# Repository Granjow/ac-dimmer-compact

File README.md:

# AC Dimmer

This is the Kicad PCB plus code for a halogen bulb dimmer
which we created for [Geheimgang 188](https://www.geheimgang.ch/).

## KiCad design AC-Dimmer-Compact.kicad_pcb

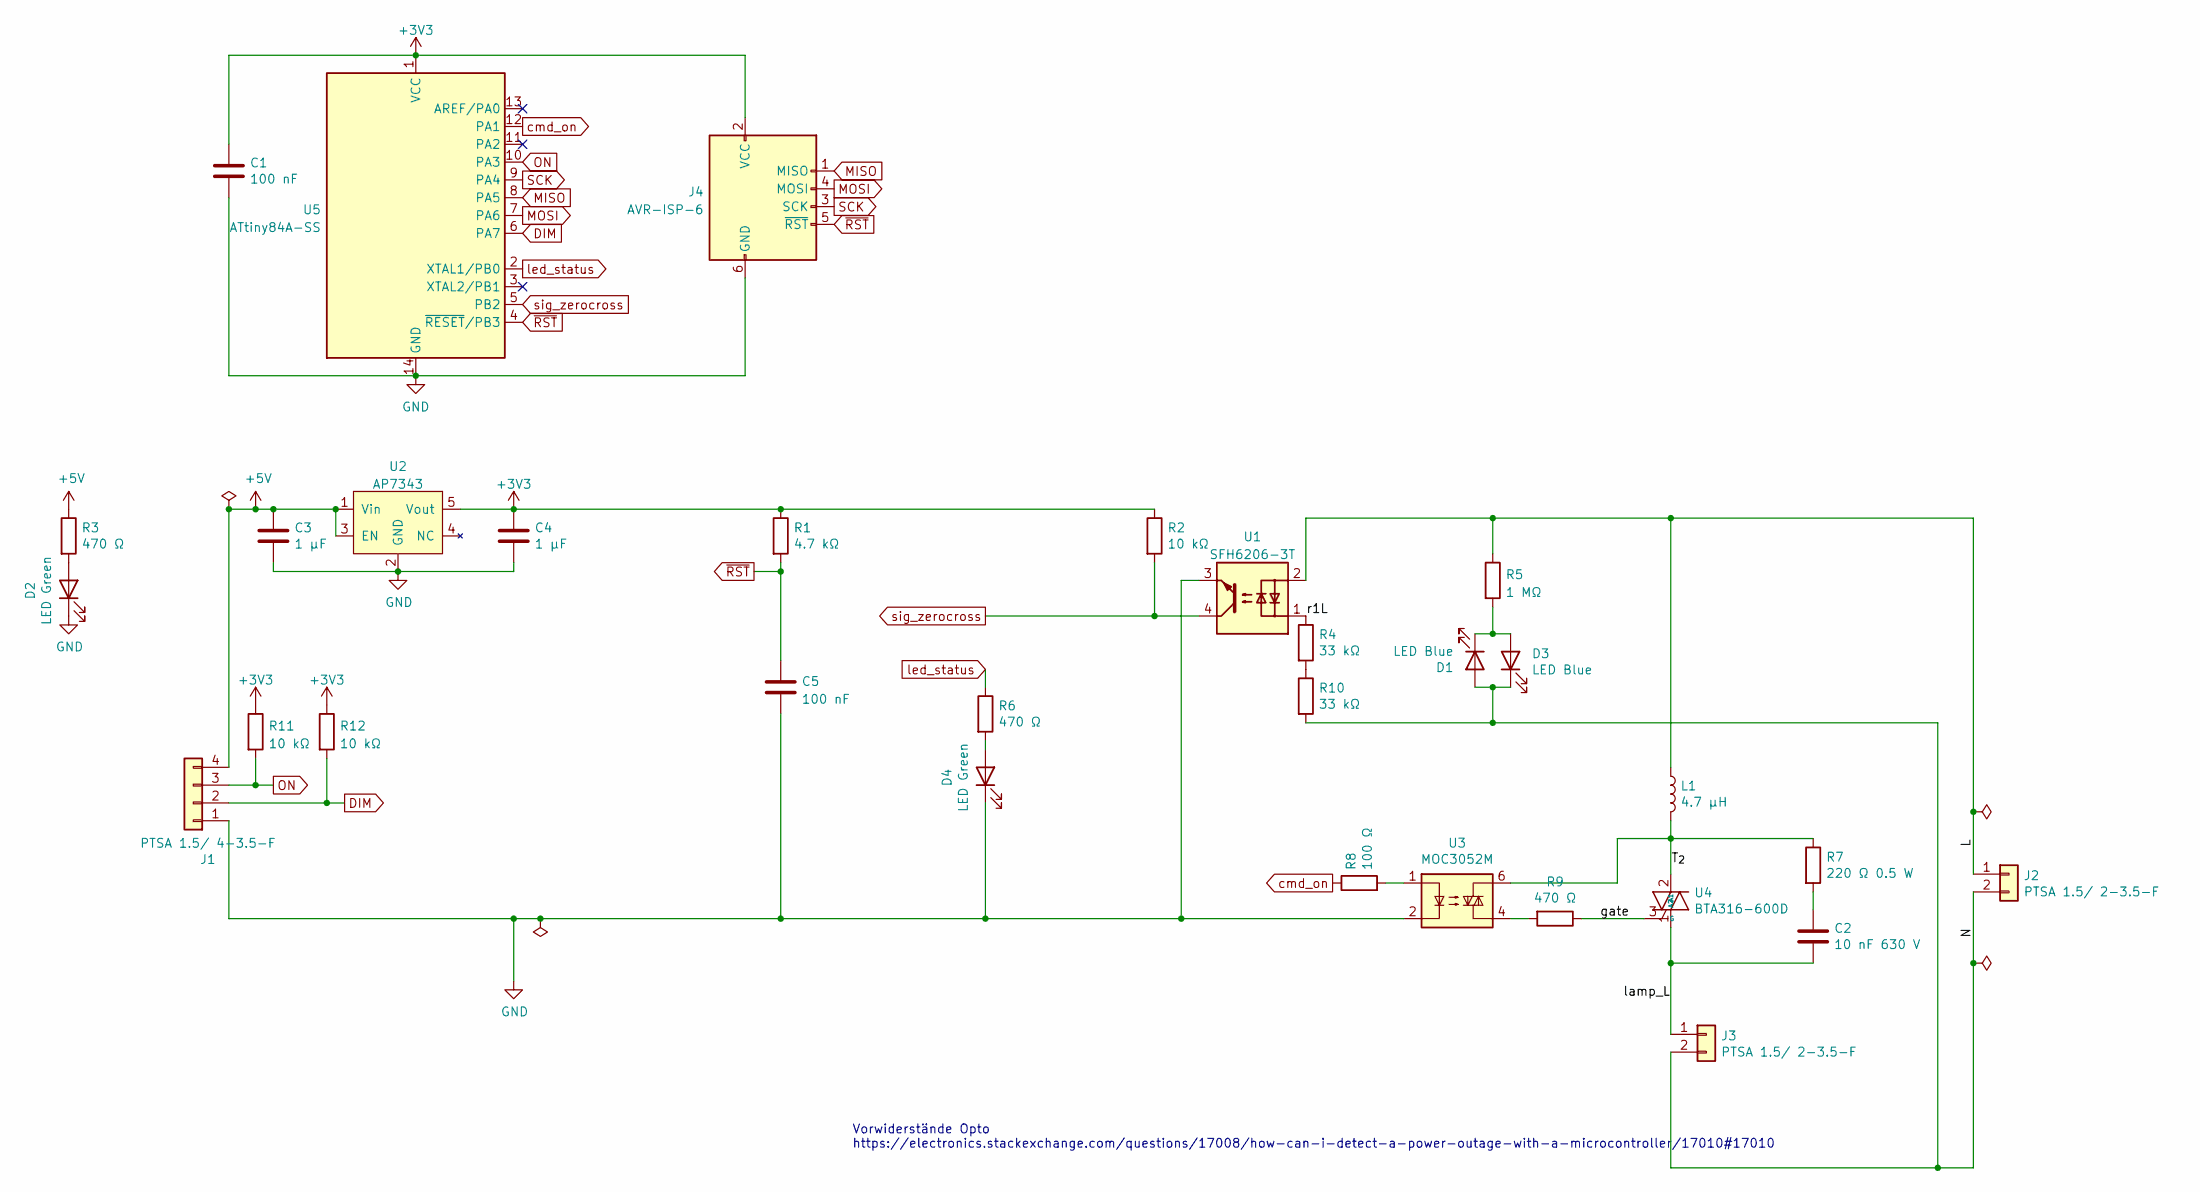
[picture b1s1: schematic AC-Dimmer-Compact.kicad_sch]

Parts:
C1, C5: 100 nF; C_0805_2012Metric_Pad1.18x1.45mm_HandSolder
C2: 10 nF 630 V; C_Rect_L7.2mm_W8.5mm_P5.00mm_FKP2_FKP2_MKS2_MKP2
C3, C4: 1 µF; C_0805_2012Metric_Pad1.15x1.40mm_HandSolder
D1, D3: LED Blue; LED_0805_2012Metric_Pad1.15x1.40mm_HandSolder
D2, D4: LED Green; LED_0805_2012Metric_Pad1.15x1.40mm_HandSolder
J1: PTSA 1.5/ 4-3.5-F; Phoenix_PTSA-1,5_1x4_P3.5mm
J2, J3: PTSA 1.5/ 2-3.5-F; Phoenix_PTSA-1,5_1x2_P3.5mm
J4: AVR-ISP-6; PinHeader_2x03_P2.54mm_Vertical
L1: 4.7 µH; 4RCC-4R7M-F18.4mm
R1: 4.7 kΩ; R_0805_2012Metric_Pad1.15x1.40mm_HandSolder
R2, R11, R12: 10 kΩ; R_0805_2012Metric_Pad1.20x1.40mm_HandSolder
R3, R6, R9: 470 Ω; R_0805_2012Metric_Pad1.15x1.40mm_HandSolder
R4, R10: 33 kΩ; R_2010_5025Metric_Pad1.40x2.65mm_HandSolder
R5: 1 MΩ; R_0805_2012Metric_Pad1.20x1.40mm_HandSolder
R7: 220 Ω 0.5 W; R_0805_2012Metric_Pad1.15x1.40mm_HandSolder
R8: 100 Ω; R_0805_2012Metric_Pad1.15x1.40mm_HandSolder
U1: SFH6206-3T; SMDIP-4_W9.53mm_Clearance8mm
U2: AP7343; SOT25
U3: MOC3052M; SMDIP-6_W9.53mm
U4: BTA316-600D; TO-220-3_Horizontal_TabDown
U5: ATtiny84A-SS; SOIC-14_3.9x8.7mm_P1.27mm

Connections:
+3V3: C1.1, C4.1, J4.2 (VCC), R1.1, R2.1, R11.1, R12.1, U2.5 (Vout), U5.1 (VCC)
+5V: C3.1, J1.4, R3.1, U2.1 (Vin), U2.3 (EN)
/L: J2.1, L1.1, R5.1, U1.2
/N: D1.2 (A), D3.1 (K), J2.2, J3.2, R10.2
/T_{2}: L1.2, R7.1, U3.6, U4.2 (A2)
/gate: R9.1, U4.3 (G)
/lamp_L: C2.2, J3.1, U4.1 (A1)
/r1L: R4.1, U1.1
DIM: J1.2, R12.2, U5.6 (PA7)
GND: C1.2, C3.2, C4.2, C5.2, D2.1 (K), D4.1 (K), J1.1, J4.6 (GND), U1.3, U2.2 (GND), U3.2, U5.14 (GND)
MISO: J4.1 (MISO), U5.8 (PA5)
MOSI: J4.4 (MOSI), U5.7 (PA6)
unnamed: C2.1, R7.2
unnamed: D1.1 (K), D3.2 (A), R5.2
unnamed: D2.2 (A), R3.2
unnamed: D4.2 (A), R6.2
unnamed: R8.2, U3.1
unnamed: R9.2, U3.4
unnamed: R4.2, R10.1
ON: J1.3, R11.2, U5.10 (PA3)
SCK: J4.3 (SCK), U5.9 (PA4)
cmd_on: R8.1, U5.12 (PA1)
led_status: R6.1, U5.2 (XTAL1/PB0)
sig_zerocross: R2.2, U1.4, U5.5 (PB2)
~RST: C5.1, J4.5 (~RST), R1.2, U5.4 (~RESET/PB3)

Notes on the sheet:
Vorwiderstände Opto https://electronics.stackexchange.com/questions/17008/how-can-i-detect-a-power-outage-with-a-microcontroller/17010#17010

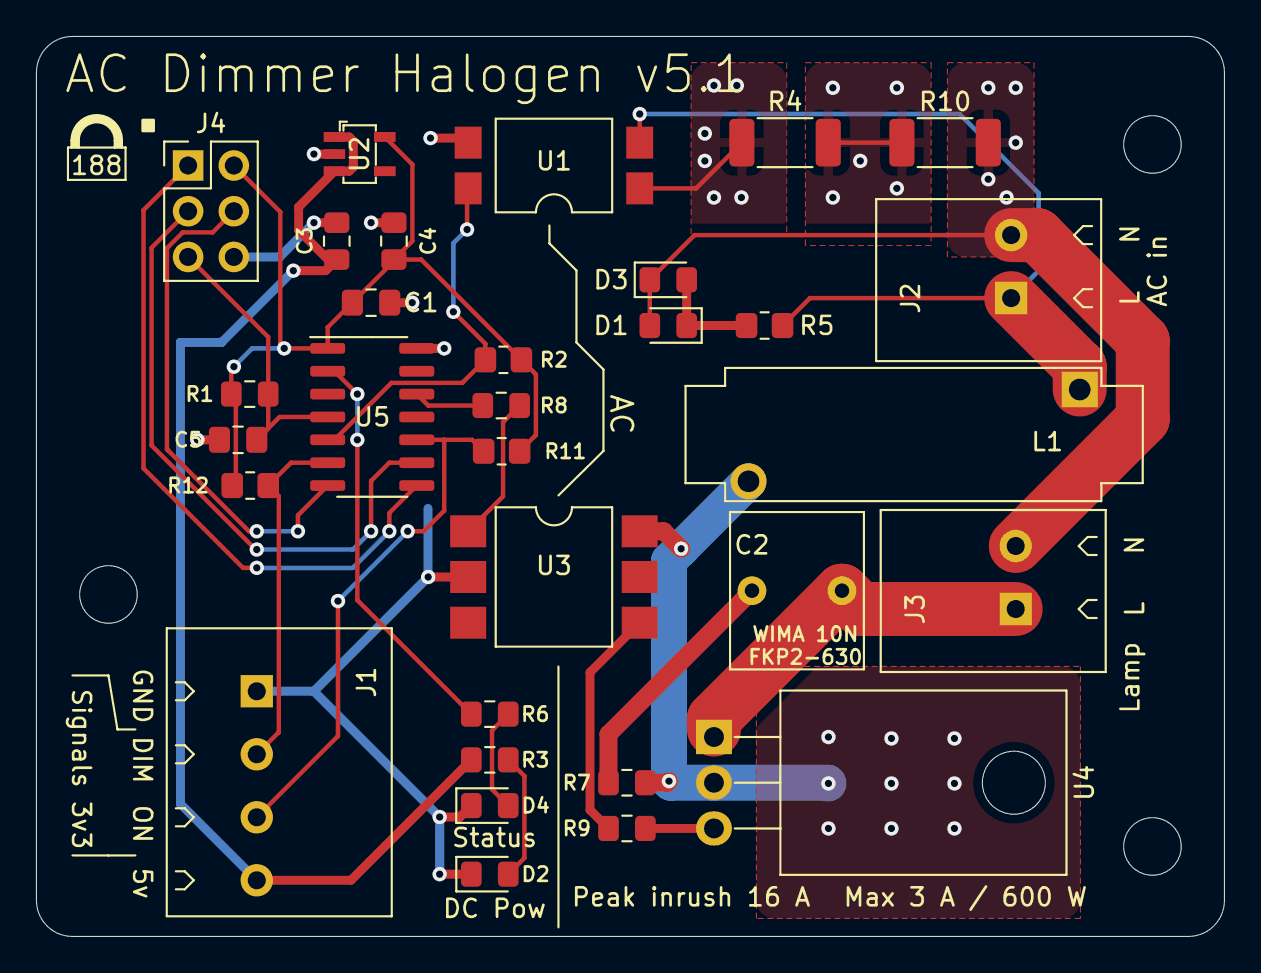
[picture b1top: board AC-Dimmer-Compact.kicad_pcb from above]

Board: 2 copper layers, 66.0 x 50.0 mm, 31 parts (0 on the bottom side), 25 nets.

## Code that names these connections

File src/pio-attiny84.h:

// ATMEL ATTINY84 / ARDUINO
//
//                           +-\/-+
//                     VCC  1|    |14  GND
//             (D 10)  PB0  2|    |13  AREF (D  0)
//             (D  9)  PB1  3|    |12  PA1  (D  1)
//                     PB3  4|    |11  PA2  (D  2)
//  PWM  INT0  (D  8)  PB2  5|    |10  PA3  (D  3)
//  PWM        (D  7)  PA7  6|    |9   PA4  (D  4)
//  PWM        (D  6)  PA6  7|    |8   PA5  (D  5)        PWM
//                           +----+

// Target IC: ATtiny84, internal 8 MHz

#ifndef PIO_ATTINY84_PIN_NAMES
#define PIO_ATTINY84_PIN_NAMES

#define PB0 (0)
#define PB1 (1)
#define PB2 (2)
#define PA7 (3)
#define PA6 (4)
#define PA5 (5)
#define PA4 (6)
#define PA3 (7)
#define PA2 (8)
#define PA1 (9)
#define PA0 (10)

#endif // PIO_ATTINY84_PIN_NAMES

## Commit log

2023-12-10 Add PCB + Code
